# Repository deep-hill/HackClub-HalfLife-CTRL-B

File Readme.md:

This is CTRL-B
The modified version of starbie, a desktop pet on a game controller base.

Features-
- Custom Digital Oled Pet
- Pet stuff like napping
- Mood based light, vibration, sound
- Time display
- Ultrasonic based measuring

Parts
- XIAO ESP32-C3
- MPU6050
- DHT11
- Cherry MX Linear Switch (×3)
- MX Keycap R2 (×3)
- 0.96" OLED SSD1306 I2C
- Resistors
- HC-SR04 Ultrasonic Sensor
- Passive Buzzer
- CR2032 Battery Holder PTH
- CR2032 Battery
- LDR GL5528
- RGB LED Common Cathode 5mm
- Vibration Motor (coin type)
- PCF8574T I2C I/O Extension Board
- TM1637 4-Digit 7-Segment Display
- PCB (custom)

It's cool.

Schematic

PCB

Attempt at custom character

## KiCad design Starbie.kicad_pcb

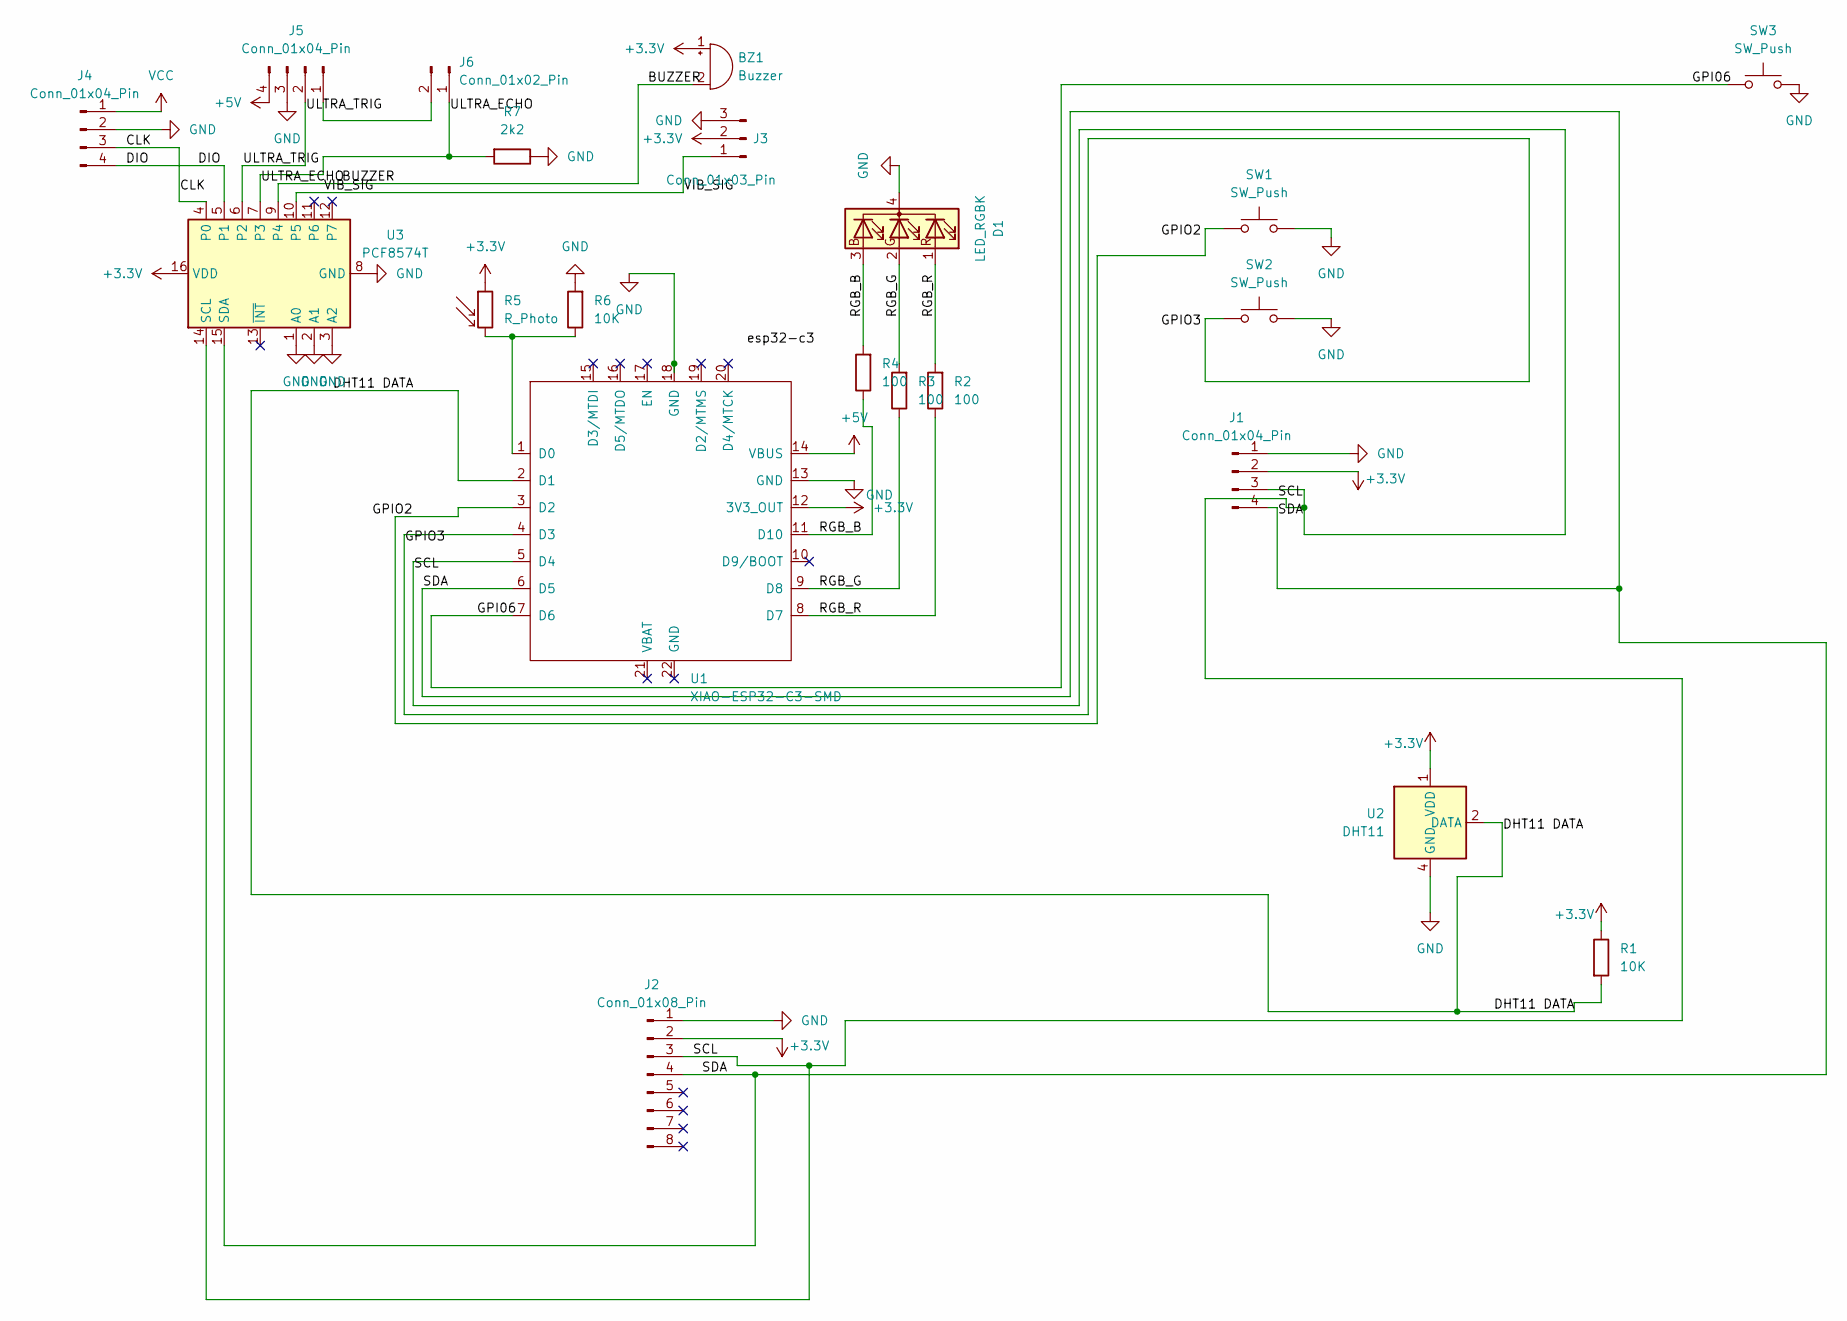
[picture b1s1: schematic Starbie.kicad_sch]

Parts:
BZ1: Buzzer; Buzzer_TDK_PS1240P02BT_D12.2mm_H6.5mm
D1: LED_RGBK; LED_D5.0mm-4_RGB_Wide_Pins
J1: Conn_01x04_Pin; Display_128x64_096_I2C
J2: Conn_01x08_Pin; PinHeader_1x08_P2.54mm_Vertical
J3: Conn_01x03_Pin; PinHeader_1x03_P2.54mm_Vertical
J4, J5: Conn_01x04_Pin; PinHeader_1x04_P2.54mm_Vertical
J6: Conn_01x02_Pin; PinHeader_1x02_P2.54mm_Vertical
R1: 10K; R_Axial_DIN0204_L3.6mm_D1.6mm_P7.62mm_Horizontal
R2, R3, R4: 100; R_Axial_DIN0207_L6.3mm_D2.5mm_P7.62mm_Horizontal
R5: R_Photo; R_Axial_DIN0207_L6.3mm_D2.5mm_P7.62mm_Horizontal
R6: 10K; R_Axial_DIN0207_L6.3mm_D2.5mm_P7.62mm_Horizontal
R7: 2k2; R_Axial_DIN0207_L6.3mm_D2.5mm_P7.62mm_Horizontal
SW1, SW2, SW3: SW_Push; SW_Cherry_MX_1.00u_PCB
U1: XIAO-ESP32-C3-SMD; XIAO-ESP32-C6-DIP
U2: DHT11; Aosong_DHT11_5.5x12.0_P2.54mm
U3: PCF8574T; DIP-16_W7.62mm

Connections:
+3.3V: BZ1.1 (+), J1.2, J2.2, J3.2, R1.1, R5.1, U1.12 (3V3_OUT), U2.1 (VDD), U3.16 (VDD)
+5V: J5.4, U1.14 (VBUS)
/BUZZER: BZ1.2 (-), U3.9 (P4)
/CLK: J4.3, U3.4 (P0)
/DHT11 DATA: R1.2, U1.2 (D1), U2.2 (DATA)
/DIO: J4.4, U3.5 (P1)
/GPI06: SW3.1, U1.7 (D6)
/GPIO2: SW1.1, U1.3 (D2)
/GPIO3: SW2.1, U1.4 (D3)
/RGB_B: D1.3 (BA), R4.1, R4.2, U1.11 (D10)
/RGB_G: D1.2 (GA), R3.1, R3.2, U1.9 (D8)
/RGB_R: D1.1 (RA), R2.1, R2.2, U1.8 (D7)
/SCL: J1.3, J2.3, U1.5 (D4), U3.14 (SCL)
/SDA: J1.4, J2.4, U1.6 (D5), U3.15 (SDA)
/ULTRA_ECHO: J6.1, R7.2, U3.7 (P3)
/ULTRA_TRIG: J5.2, U3.6 (P2)
/VIB_SIG: J3.1, U3.10 (P5)
GND: D1.4 (K), J1.1, J2.1, J3.3, J4.2, J5.3, R6.2, R7.1, SW1.2, SW2.2, SW3.2, U1.13 (GND), U1.18 (GND), U2.4 (GND), U3.1 (A0), U3.2 (A1), U3.3 (A2), U3.8 (GND)
unnamed: J5.1, J6.2
unnamed: R5.2, R6.1, U1.1 (D0)
VCC: J4.1

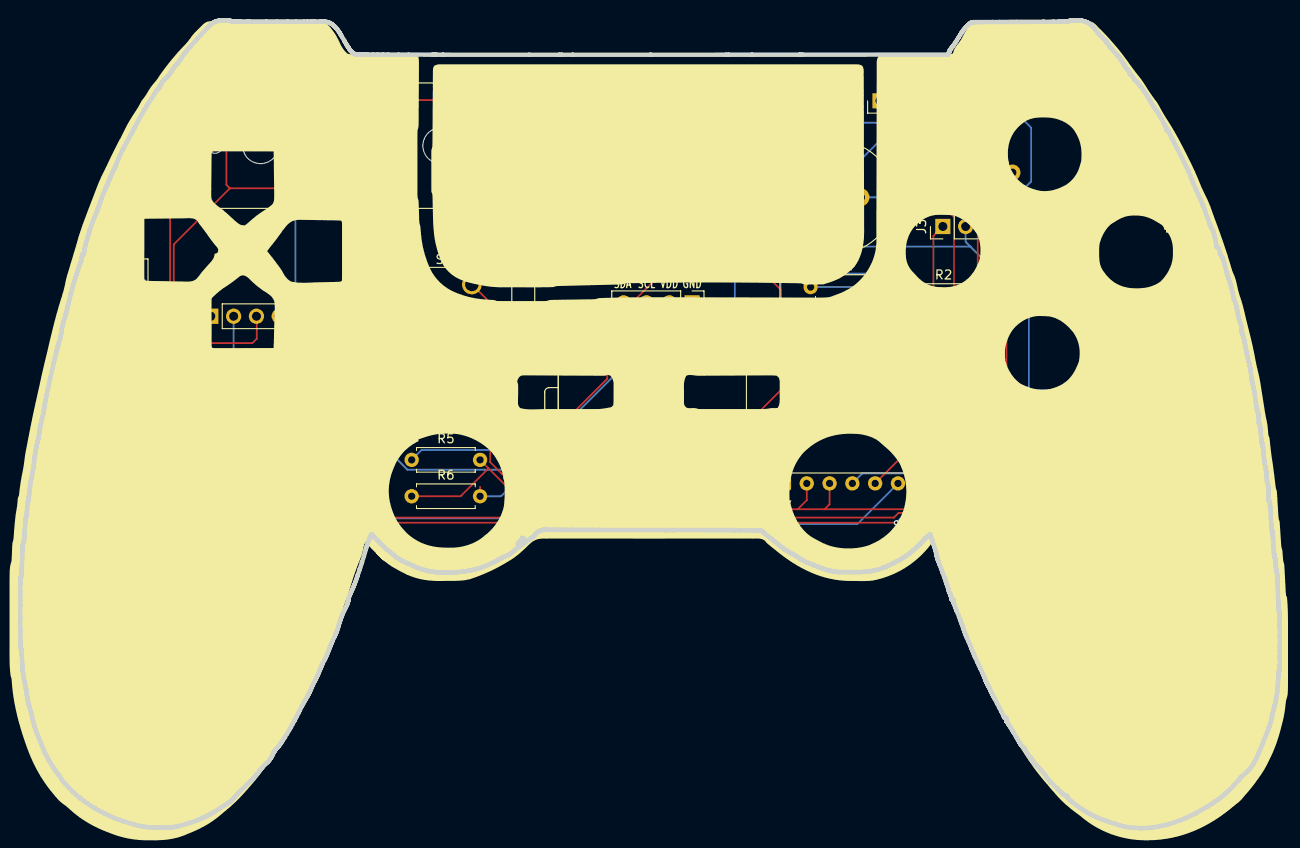
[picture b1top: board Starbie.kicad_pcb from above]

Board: 2 copper layers, 140.3 x 90.0 mm, 21 parts (0 on the bottom side), 20 nets.

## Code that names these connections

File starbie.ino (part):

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#define BTN2_PIN      4   // D3 - Button 2
#define BTN3_PIN      7   // D6 - Button 3 (ultrasonic trigger)
#define LDR_PIN       1   // D0 - LDR analog
#define RGB_R_PIN     8   // D7
#define RGB_G_PIN     9   // D8
#define RGB_B_PIN     11  // D10

// PCF8574T pins (via I2C expander at address 0x20)
#define PCF_DISP_CLK  0   // P0 - TM1637 CLK
#define PCF_DISP_DIO  1   // P1 - TM1637 DIO
#define PCF_TRIG      2   // P2 - HC-SR04 TRIG
#define PCF_ECHO      3   // P3 - HC-SR04 ECHO
#define PCF_BUZZER    4   // P4 - Passive buzzer
#define PCF_VIB       5   // P5 - Vibration motor

// ============================================================
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
void setRGB(int r, int g, int b) {
  // Common cathode - HIGH = on
  analogWrite(RGB_R_PIN, r);
  analogWrite(RGB_G_PIN, g);
  analogWrite(RGB_B_PIN, b);
}

// Mood colors
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  pinMode(BTN2_PIN, INPUT_PULLUP);
  pinMode(BTN3_PIN, INPUT_PULLUP);
  pinMode(LDR_PIN,  INPUT);
  pinMode(RGB_R_PIN, OUTPUT);
  pinMode(RGB_G_PIN, OUTPUT);
  pinMode(RGB_B_PIN, OUTPUT);

  // I2C
  Wire.begin();
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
